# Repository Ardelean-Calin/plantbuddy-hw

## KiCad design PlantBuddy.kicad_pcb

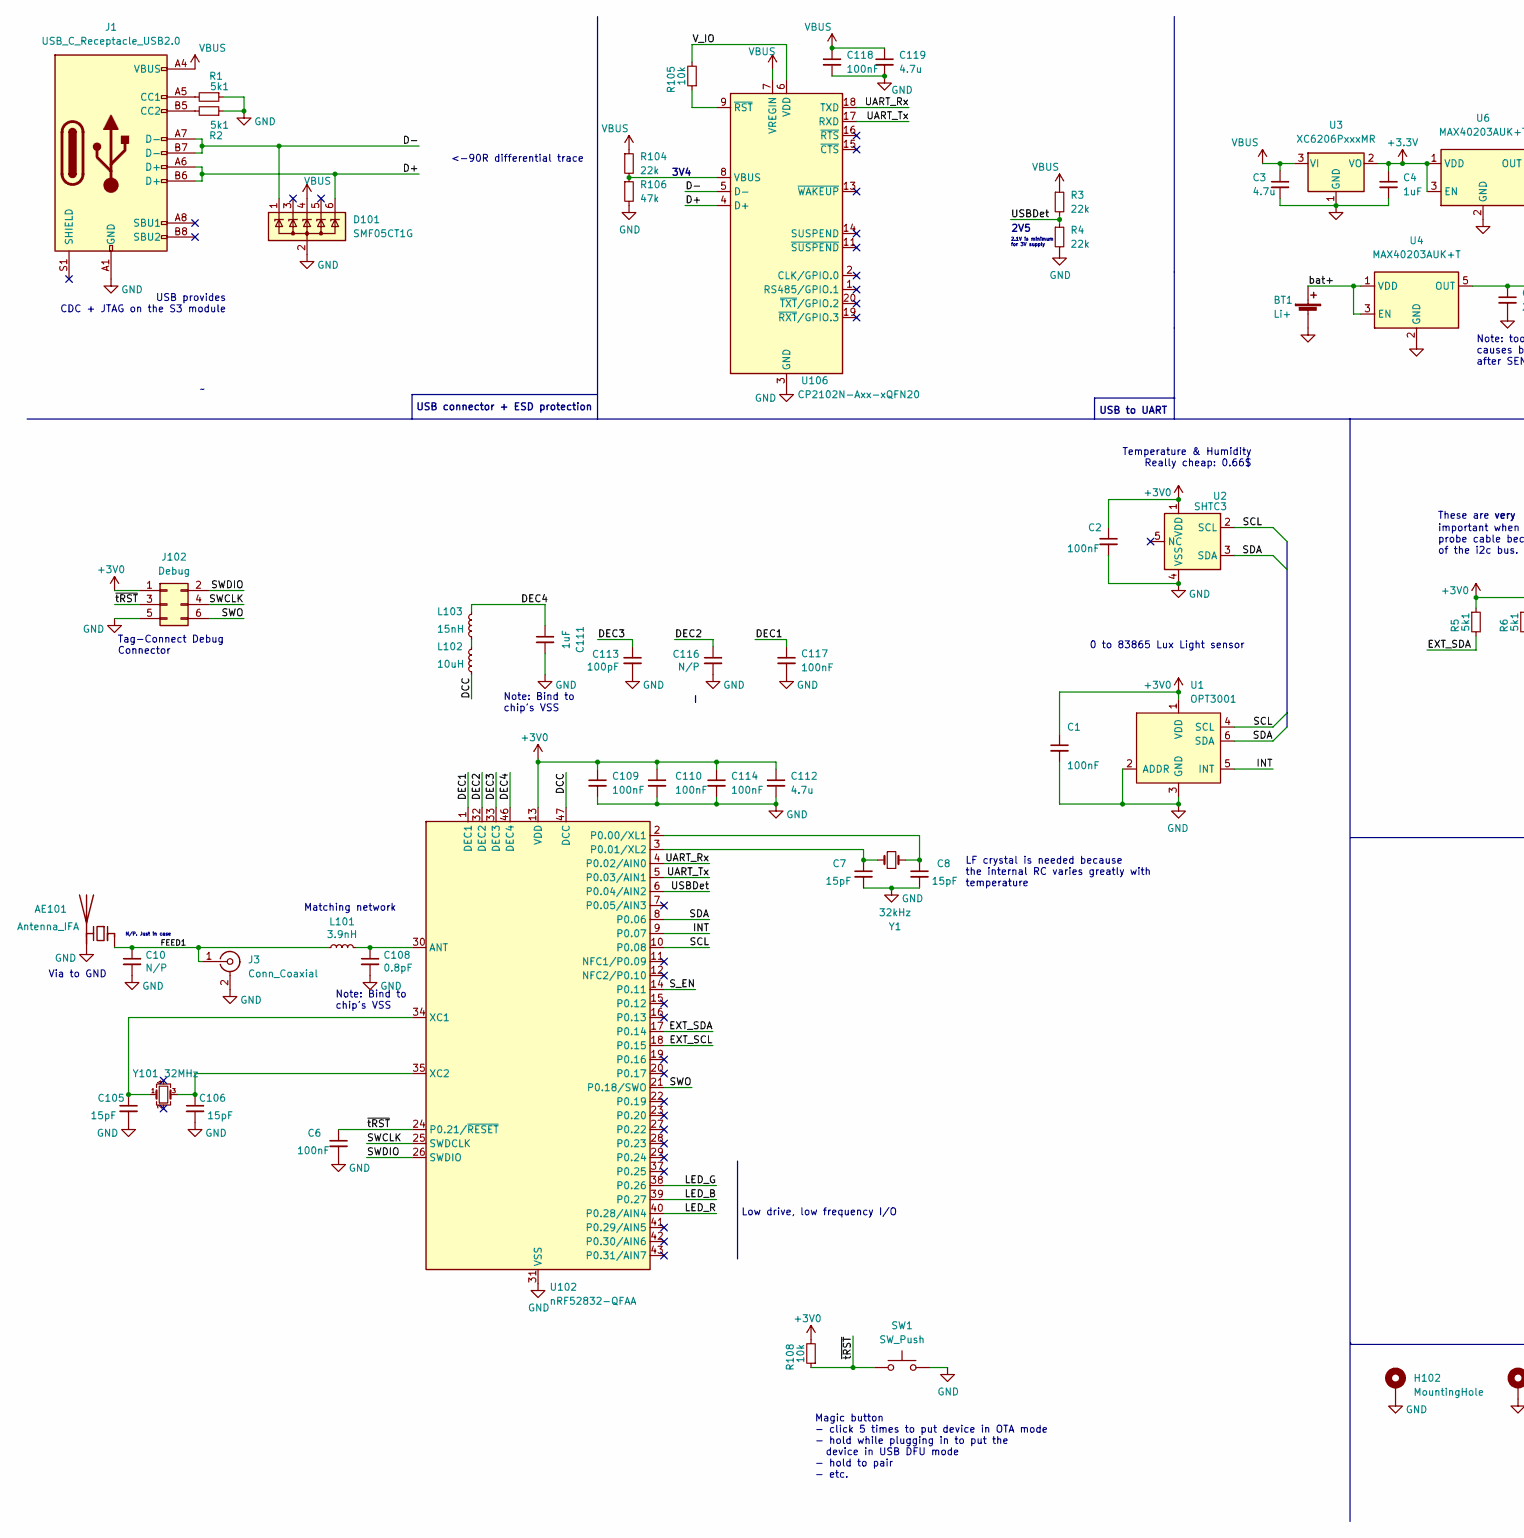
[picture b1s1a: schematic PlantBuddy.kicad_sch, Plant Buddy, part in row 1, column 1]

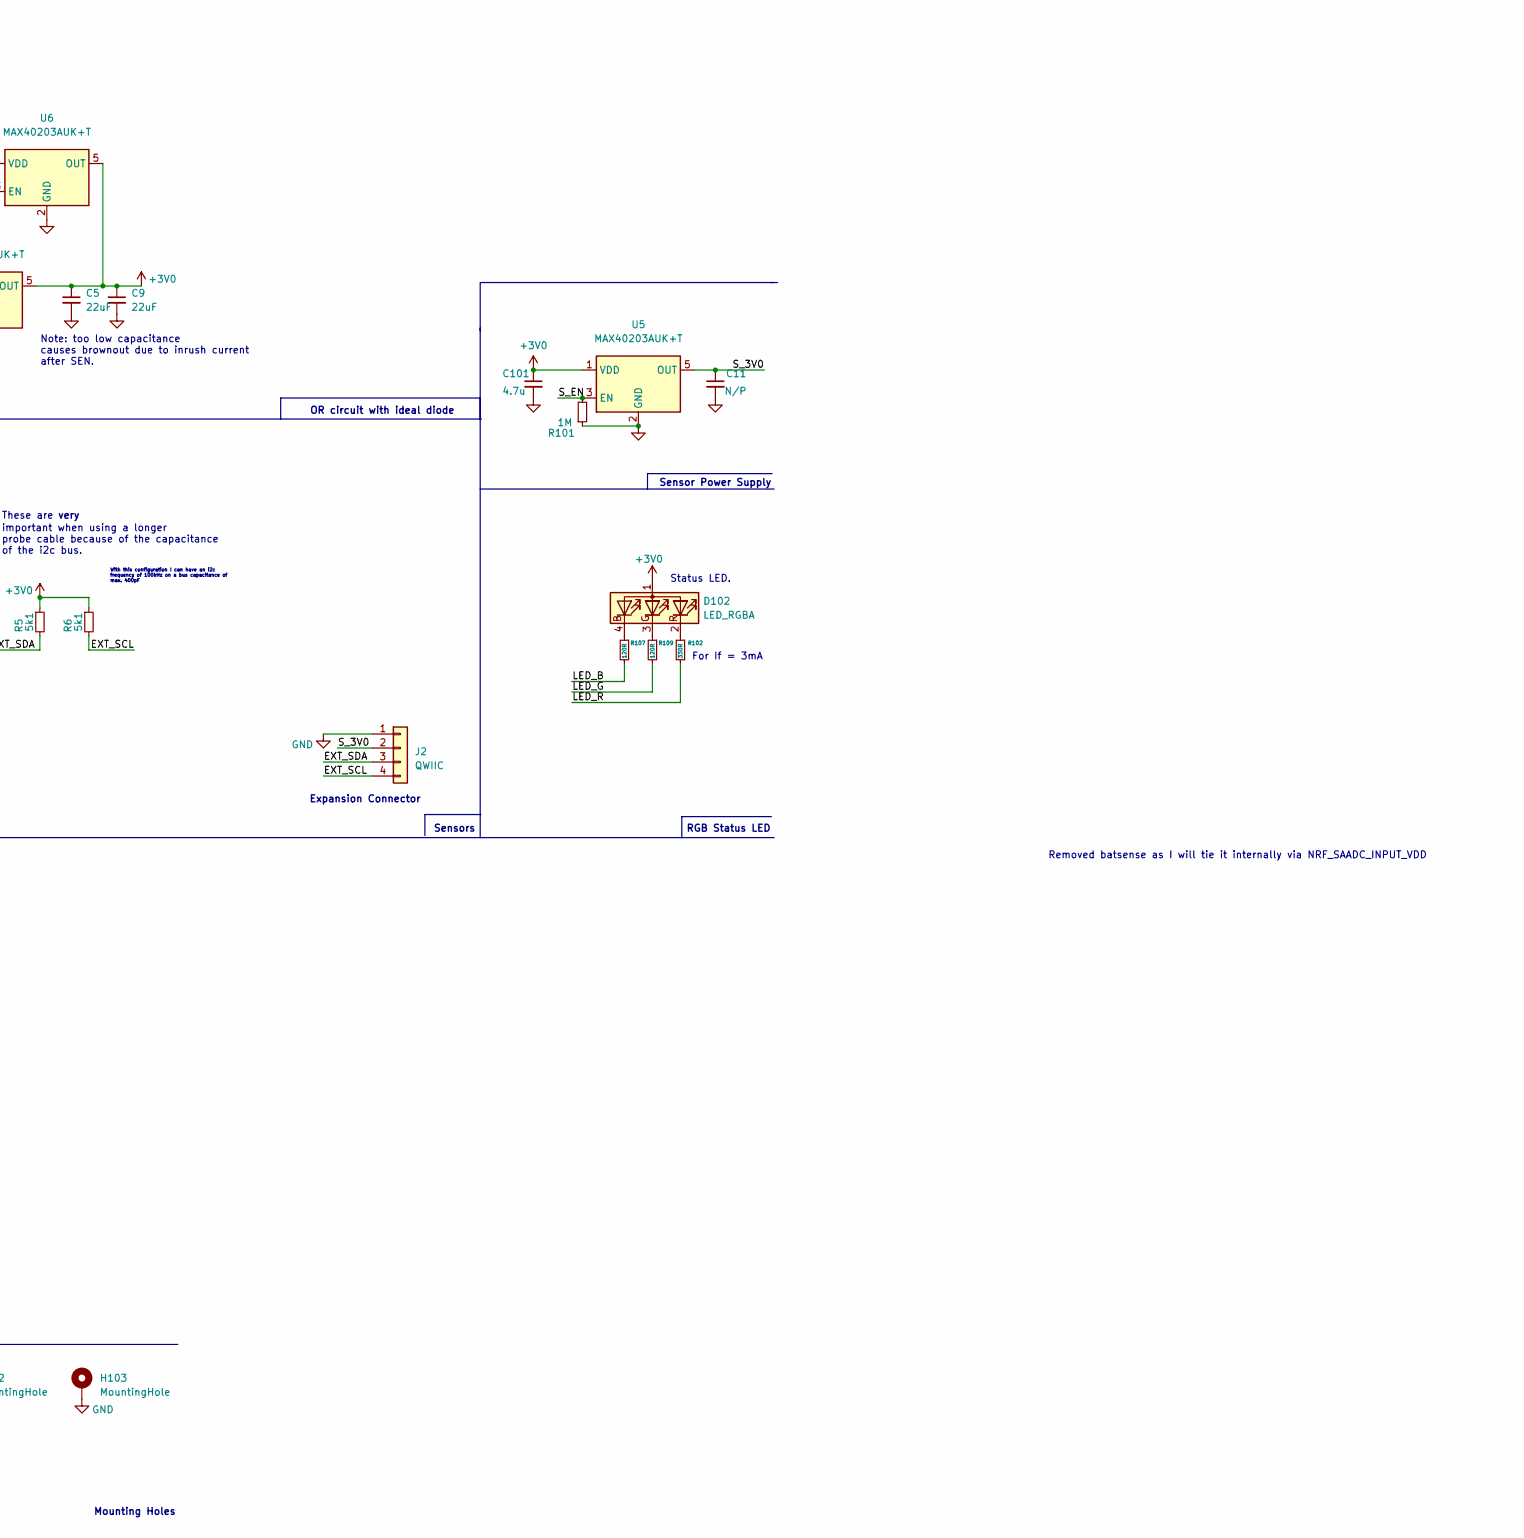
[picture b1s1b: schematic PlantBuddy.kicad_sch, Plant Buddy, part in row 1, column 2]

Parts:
AE101: Antenna_IFA; ANT-F-1-2.4G-1.6MM-FR4-WCH
BT1: Li+; BatteryHolder_LCSC_2032; LCSC C70377
C1, C2, C109, C110, C114, C117, C118: 100nF; C_0402_1005Metric; MPN CC0603KRX7R9BB104; LCSC C307331
C3, C101, C112, C119: 4.7u; C_0402_1005Metric; MPN CL10A475KO8NNNC; LCSC C23733
C4: 1uF; C_0402_1005Metric; MPN CL10A475KO8NNNC; LCSC C52923
C5, C9: 22uF; C_0603_1608Metric; MPN CL10A475KO8NNNC; LCSC C59461
C6: 100nF; C_0402_1005Metric; MPN CL10A475KO8NNNC; LCSC C307331
C7, C8, C105, C106: 15pF; C_0402_1005Metric; LCSC C1548
C10, C116: N/P; C_0402_1005Metric
C11: N/P; C_0402_1005Metric; MPN CL10A475KO8NNNC
C108: 0.8pF; C_0402_1005Metric; LCSC C172820
C111: 1uF; C_0402_1005Metric; MPN CC0603KRX7R9BB104; LCSC C52923
C113: 100pF; C_0402_1005Metric; LCSC C1546
D101: SMF05CT1G; SOT-363_SC-70-6; LCSC C15879
D102: LED_RGBA; LED_Lumex_SML-LX0404SIUPGUSB; LCSC C404280
H102, H103: MountingHole; MountingHole_3.2mm_M3_DIN965_Pad
J1: USB_C_Receptacle_USB2.0; USB_C_Receptacle_HRO_TYPE-C-31-M-12; MPN TYPE-C-31-M-12; LCSC C165948
J2: QWIIC; JST_SH_SM04B-SRSS-TB_1x04-1MP_P1.00mm_Horizontal; LCSC C160404
J3: Conn_Coaxial; U.FL_Hirose_U.FL-R-SMT-1_Vertical; LCSC C88374
J102: Debug; Tag-Connect_TC2030-IDC-NL_2x03_P1.27mm_Vertical
L101: 3.9nH; L_0402_1005Metric; LCSC C76775
L102: 10uH; L_0603_1608Metric; LCSC C223240
L103: 15nH; L_0402_1005Metric; LCSC C27143
R1, R2, R5, R6: 5k1; R_0402_1005Metric; MPN 0603WAF5101T5E; LCSC C25905
R3, R4, R104: 22k; R_0402_1005Metric; LCSC C25768
R101: 1M; R_0402_1005Metric; MPN 0603WAF2004T5E; LCSC C26083
R102: 330R; R_0402_1005Metric; LCSC C25104
R105, R108: 10k; R_0402_1005Metric; MPN 0603WAF5101T5E; LCSC C25744
R106: 47k; R_0402_1005Metric; LCSC C25792
R107, R109: 120R; R_0402_1005Metric; LCSC C25079
SW1: SW_Push; SW_Push_SPST_NO_Alps_SKRK; MPN SKRKAEE020; LCSC C115357
U1: OPT3001; SON65P200X200X65-7N; LCSC C90462
U2: SHTC3; SON100P200X200X80-5N; MPN SHTC3; LCSC C194656
U3: XC6206PxxxMR; SOT-23; LCSC C5446
U4, U5, U6: MAX40203AUK+T; SOT-23-5; LCSC C2653639
U102: nRF52832-QFAA; QFN-48-1EP_6x6mm_P0.4mm_EP4.6x4.6mm; LCSC C77540
U106: CP2102N-Axx-xQFN20; SiliconLabs_QFN-20-1EP_3x3mm_P0.5mm_EP1.8x1.8mm; LCSC C969913
Y1: 32kHz; Crystal_SMD_3215-2Pin_3.2x1.5mm; LCSC C32346
Y101: 32MHz; Crystal_SMD_3225-4Pin_3.2x2.5mm; LCSC C90934

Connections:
+3.3V: C4.1, U3.2 (VO), U6.1 (VDD), U6.3 (EN)
+3V0: C1.1, C2.1, C5.1, C9.1, C101.1, C109.1, C110.1, C112.1, C114.1, D102.1 (A), J102.1, R5.1, R6.1, R108.2, U1.1 (VDD), U2.1 (VDD), U4.5 (OUT), U5.1 (VDD), U6.5 (OUT), U102.13 (VDD), U102.36 (VDD), U102.48 (VDD)
/D+: D101.6 (K), J1.A6 (D+), J1.B6 (D+), U106.4 (D+)
/D-: D101.1 (K), J1.A7 (D-), J1.B7 (D-), U106.5 (D-)
/DCC: L102.2, U102.47 (DCC)
/DEC1: C117.1, U102.1 (DEC1)
/DEC2: C116.1, U102.32 (DEC2)
/DEC3: C113.1, U102.33 (DEC3)
/DEC4: C111.1, L103.1, U102.46 (DEC4)
/EXT_SCL: J2.4, R6.2, U102.18 (P0.15)
/EXT_SDA: J2.3, R5.2, U102.17 (P0.14)
/FEED1: AE101.1 (FEED), C10.1, J3.1 (In), L101.1
/INT: U1.5 (INT), U102.9 (P0.07)
/LED_B: R107.2, U102.39 (P0.27)
/LED_G: R109.2, U102.38 (P0.26)
/LED_R: R102.2, U102.40 (P0.28/AIN4)
/SCL: U1.4 (SCL), U2.2 (SCL), U102.10 (P0.08)
/SDA: U1.6 (SDA), U2.3 (SDA), U102.8 (P0.06)
/SWCLK: J102.4, U102.25 (SWDCLK)
/SWDIO: J102.2, U102.26 (SWDIO)
/SWO: J102.6, U102.21 (P0.18/SWO)
/S_3V0: C11.1, J2.2, U5.5 (OUT)
/S_EN: R101.2, U5.3 (EN), U102.14 (P0.11)
/UART_Rx: U102.4 (P0.02/AIN0), U106.18 (TXD)
/UART_Tx: U102.5 (P0.03/AIN1), U106.17 (RXD)
/USBDet: R3.2, R4.1, U102.6 (P0.04/AIN2)
/V_IO: R105.2, U106.6 (VDD)
/bat+: BT1.1 (+), U4.1 (VDD), U4.3 (EN)
/~tRST: C6.1, J102.3, R108.1, SW1.1, U102.24 (P0.21/~RESET)
GND: AE101.2 (PCB_Trace), BT1.2 (-), C1.2, C2.2, C3.2, C4.2, C5.2, C6.2, C7.2, C8.2, C9.2, C10.2, C11.2, C101.2, C105.2, C106.2, C108.2, C109.2, C110.2, C111.2, C112.2, C113.2, C114.2, C116.2, C117.2, C118.2, C119.2, D101.2 (A), H102.1, H103.1, J1.A1 (GND), J1.A12 (GND), J1.B1 (GND), J1.B12 (GND), J2.1, J3.2 (Ext), J102.5, R1.1, R2.1, R4.2, R101.1, R106.2, SW1.2, U1.2 (ADDR), U1.3 (GND), U1.7 (PAD), U2.4 (VSS), U3.1 (GND), U4.2 (GND), U5.2 (GND), U6.2 (GND), U102.31 (VSS), U102.45 (VSS), U102.49 (VSS), U106.3 (GND), U106.12 (GND), U106.21 (GND)
unnamed: D102.4 (BK), R107.1
unnamed: D102.3 (GK), R109.1
unnamed: D102.2 (RK), R102.1
unnamed: J1.A5 (CC1), R1.2
unnamed: J1.B5 (CC2), R2.2
unnamed: L102.1, L103.2
unnamed: C108.1, L101.2, U102.30 (ANT)
unnamed: C8.1, U102.2 (P0.00/XL1), Y1.2
unnamed: C7.1, U102.3 (P0.01/XL2), Y1.1
unnamed: C105.1, U102.34 (XC1), Y101.1
unnamed: C106.1, U102.35 (XC2), Y101.3
unnamed: R104.2, R106.1, U106.8 (VBUS)
unnamed: R105.1, U106.9 (~RST)
VBUS: C3.1, C118.1, C119.1, D101.4 (K), J1.A4 (VBUS), J1.A9 (VBUS), J1.B4 (VBUS), J1.B9 (VBUS), R3.1, R104.1, U3.3 (VI), U106.7 (VREGIN)

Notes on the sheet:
very
Sensors
Note: too low capacitance causes brownout due to inrush current after SEN.
These are
USB provides CDC + JTAG on the S3 module
Magic button - click 5 times to put device in OTA mode - hold while plugging in to put the device in USB DFU mode - hold to pair - etc.
Via to GND
RGB Status LED
Tag-Connect Debug Connector
Expansion Connector
Removed batsense as I will tie it internally via NRF_SAADC_INPUT_VDD
Sensor Power Supply
2.1V is minimum for 3V supply
important when using a longer probe cable because of the capacitance of the i2c bus.
Low drive, low frequency I/O
Note: Bind to chip's VSS
3V4
<-90R differential trace
0 to 83865 Lux Light sensor
Temperature & Humidity Really cheap: 0.66$
With this configuration I can have an i2c frequency of 100kHz on a bus capacitance of max. 400pF
Matching network
Mounting Holes
For If = 3mA
LF crystal is needed because the internal RC varies greatly with temperature
2V5
OR circuit with ideal diode
Status LED.
N/P. Just in case
USB connector + ESD protection
USB to UART

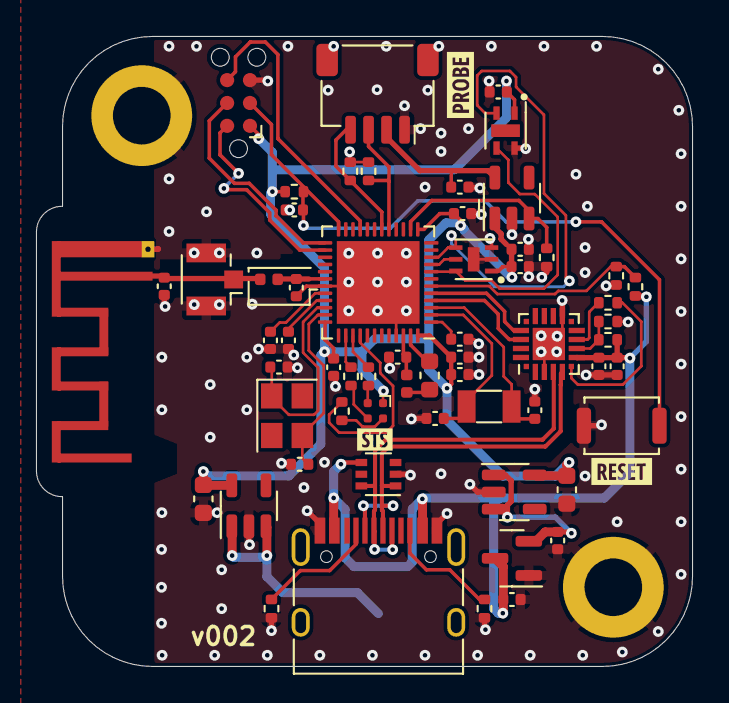
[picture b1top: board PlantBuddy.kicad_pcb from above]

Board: 4 copper layers, 36.4 x 35.0 mm, 63 parts (1 on the bottom side), 44 nets.

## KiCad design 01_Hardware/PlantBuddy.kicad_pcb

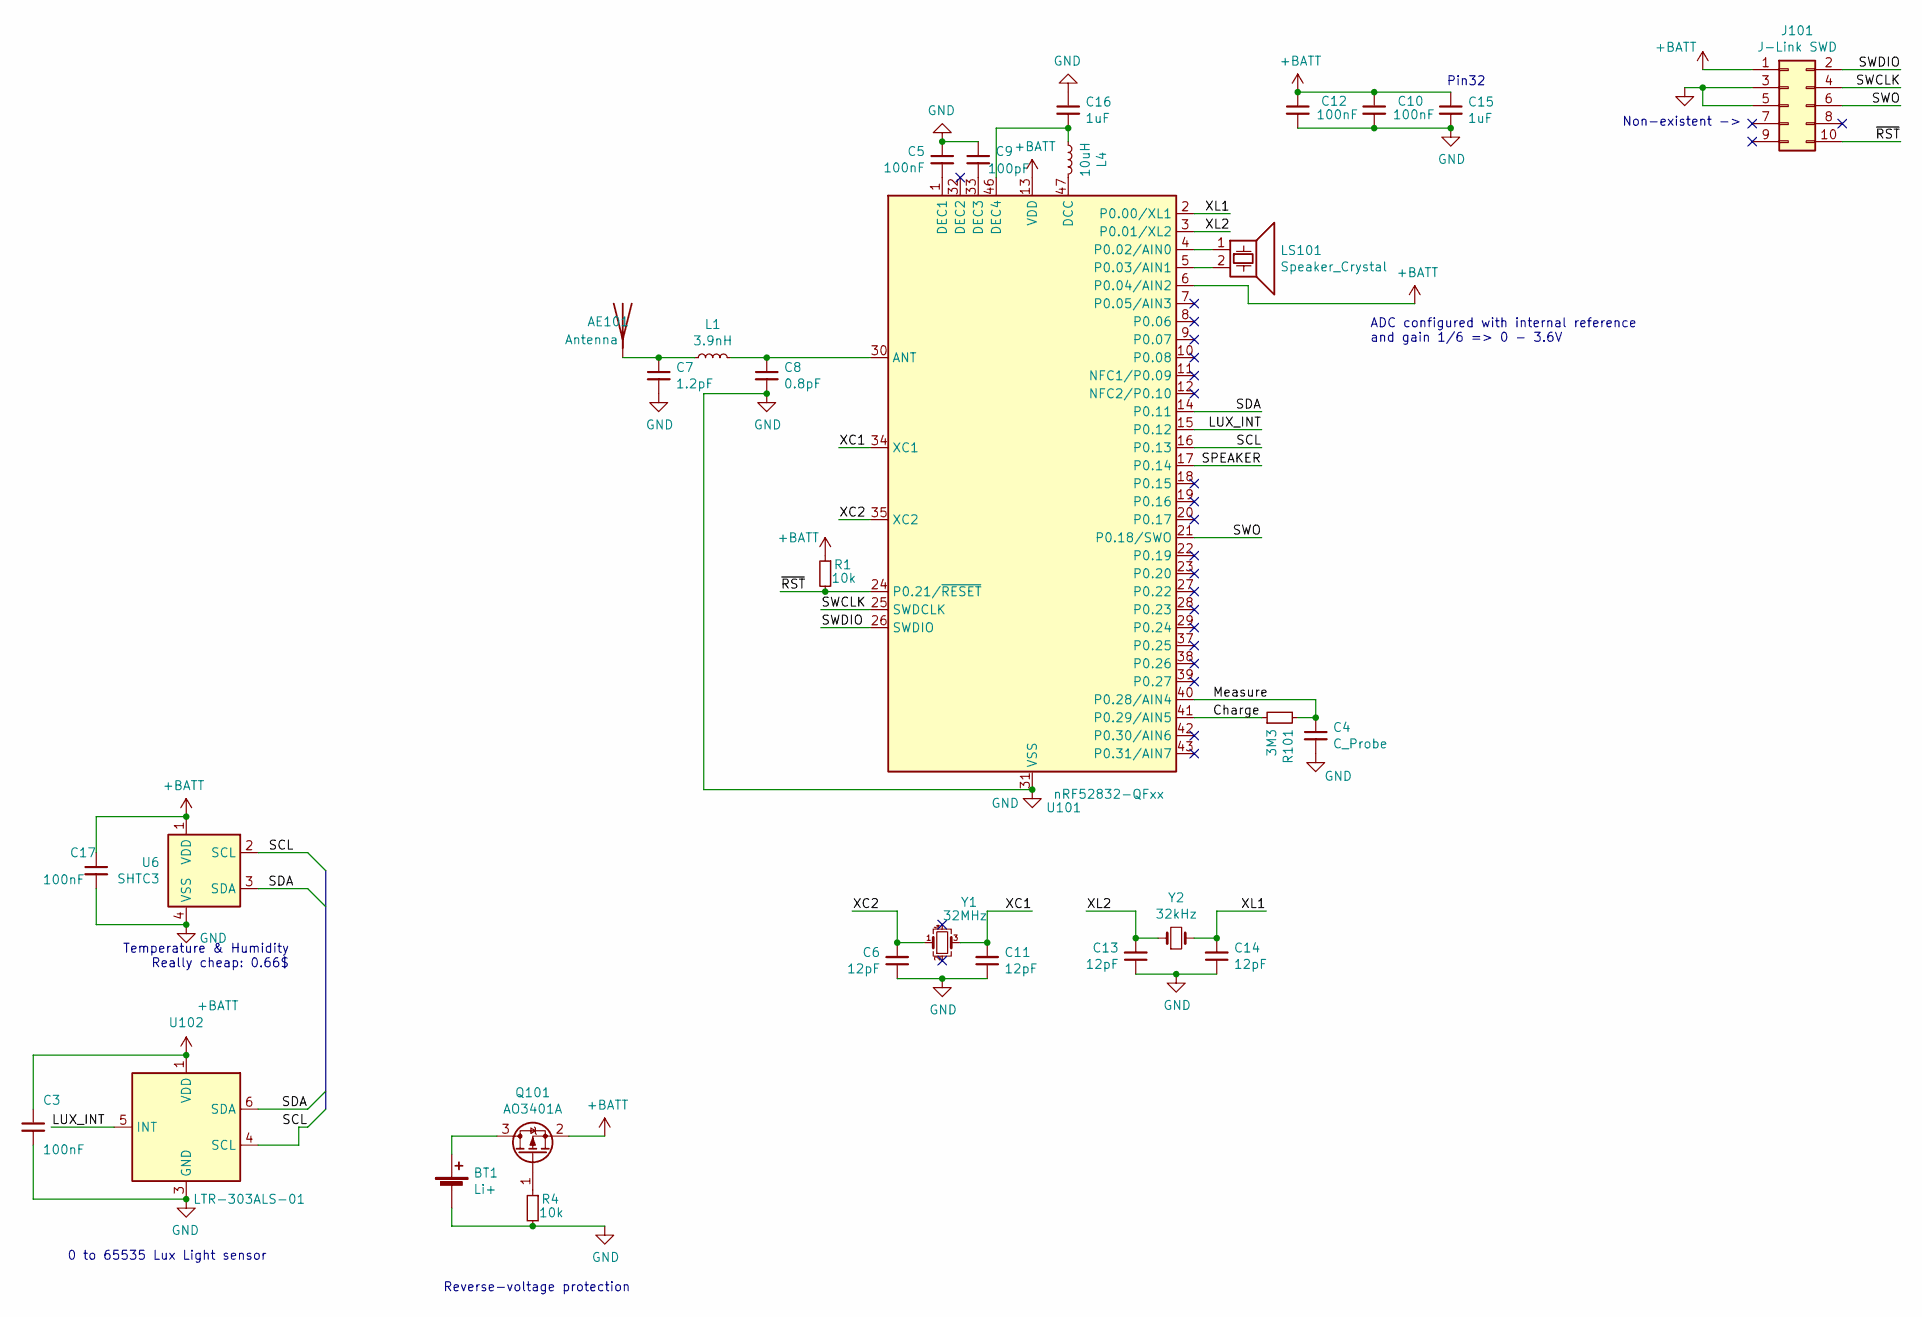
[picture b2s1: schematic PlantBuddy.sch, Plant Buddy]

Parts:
AE101: Antenna; monopole
BT1: Li+; BAT-HLD-001
C3, C5, C10, C12, C17: 100nF; C_0603_1608Metric; LCSC C1525
C4: C_Probe; SoilProbe
C6, C11, C13, C14: 12pF; C_0603_1608Metric; LCSC C1547
C7: 1.2pF; C_0402_1005Metric; LCSC C159809
C8: 0.8pF; C_0402_1005Metric; LCSC C285068
C9: 100pF; C_0402_1005Metric; LCSC C1546
C15, C16: 1uF; C_0603_1608Metric; LCSC C52923
J101: J-Link SWD; PinHeader_2x05_P1.27mm_Vertical_SMD
L1: 3.9nH; L_0402_1005Metric; LCSC C14033
L4: 10uH; L_0805_2012Metric; LCSC C95978
LS101: Speaker_Crystal; PinHeader_1x02_P2.54mm_Vertical
Q101: AO3401A; SOT-23
R1, R4: 10k; R_0603_1608Metric; LCSC C25744
R101: 3M3; R_0603_1608Metric; LCSC C25741
U6: SHTC3; Sensirion_DFN-4-1EP_2x2mm_P1mm_EP0.7x1.6mm; LCSC C194656
U101: nRF52832-QFxx; QFN-48-1EP_6x6mm_P0.4mm_EP4.6x4.6mm_ThermalVias
U102: LTR-303ALS-01; Lite-On_LTR-303ALS-01
Y1: 32MHz; Crystal_SMD_3225-4Pin_3.2x2.5mm; LCSC C90934
Y2: 32kHz; Crystal_SMD_3215-2Pin_3.2x1.5mm; LCSC C32346

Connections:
+BATT: C3.1, C10.1, C12.1, C15.1, C17.1, J101.1, Q101.2 (S), R1.1, U6.1 (VDD), U101.6 (P0.04/AIN2), U101.13 (VDD), U101.36 (VDD), U101.48 (VDD), U102.1 (VDD)
/Charge: R101.1, U101.41 (P0.29/AIN5)
/LUX_INT: U101.15 (P0.12), U102.5 (INT)
/Measure: C4.1, R101.2, U101.40 (P0.28/AIN4)
/SCL: U6.2 (SCL), U101.16 (P0.13), U102.4 (SCL)
/SDA: U6.3 (SDA), U101.14 (P0.11), U102.6 (SDA)
/SPEAKER: U101.17 (P0.14)
/SWCLK: J101.4, U101.25 (SWDCLK)
/SWDIO: J101.2, U101.26 (SWDIO)
/SWO: J101.6, U101.21 (P0.18/SWO)
/XC1: C11.2, U101.34 (XC1), Y1.3
/XC2: C6.2, U101.35 (XC2), Y1.1
/XL1: C14.2, U101.2 (P0.00/XL1), Y2.2
/XL2: C13.2, U101.3 (P0.01/XL2), Y2.1
/~RST: J101.10, R1.2, U101.24 (P0.21/~RESET)
GND: BT1.2 (-), C3.2, C4.2, C5.1, C6.1, C7.2, C8.2, C9.1, C10.2, C11.1, C12.2, C13.1, C14.1, C15.2, C16.1, C17.2, J101.3, J101.5, R4.2, U6.4 (VSS), U101.31 (VSS), U101.45 (VSS), U101.49 (VSS), U102.3 (GND)
unnamed: AE101.1, C7.1, L1.1
unnamed: BT1.1 (+), Q101.3 (D)
unnamed: C5.2, U101.1 (DEC1)
unnamed: C8.1, L1.2, U101.30 (ANT)
unnamed: C9.2, U101.33 (DEC3)
unnamed: C16.2, L4.1, U101.46 (DEC4)
unnamed: L4.2, U101.47 (DCC)
unnamed: LS101.1, U101.4 (P0.02/AIN0)
unnamed: LS101.2, U101.5 (P0.03/AIN1)
unnamed: Q101.1 (G), R4.1

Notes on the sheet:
Temperature & Humidity Really cheap: 0.66$
Reverse-voltage protection
0 to 65535 Lux Light sensor
ADC configured with internal reference and gain 1/6 => 0 - 3.6V
Pin32
Non-existent ->

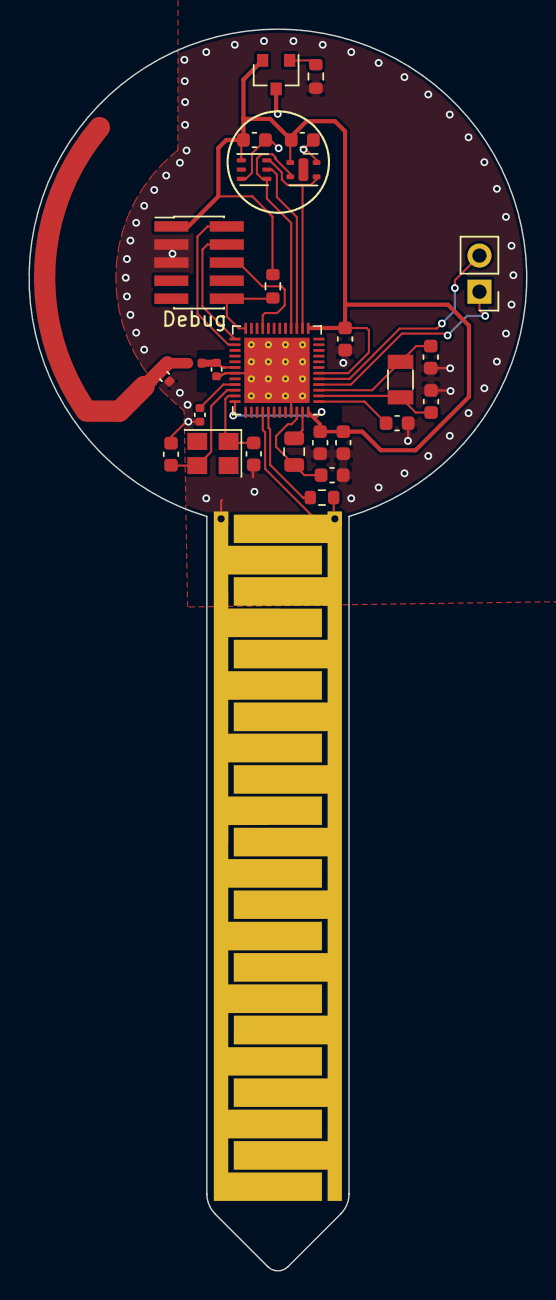
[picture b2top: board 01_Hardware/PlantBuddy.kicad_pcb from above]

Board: 2 copper layers, 35.0 x 87.3 mm, 30 parts (1 on the bottom side), 25 nets.

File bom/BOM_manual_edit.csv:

Comment,Designator,Footprint,LCSC Part Number
1.2pF,C7,0402,C159809
0.8pF,C8,0402,C285068
100pF,C9,0603,C14858
100nF,"C3,C5,C10,C12,C17",0603,C14663
12pF,"C6,C11,C13,C14",0603,C38523
1uF,"C15,C16",0603,C15849
SWD Debug port,J101,HDR-SMD,C150517
3.9nH,L1,0402,C14033
10uH,L4,0805,C1046
P-Channel Mosfet,Q101,SOT-23-3L,C15127
10k,"R1,R4",0603,C25804
0 Ohm,R101,0603,C21189
10 Ohm,R102,0603,C22859
Temperature & humidity,U6,DFN-4,C194656
"Nordig nRF52 SoC I2C, SPI, UART 4dBm 1.7V ~ 3.6V TxRx + MCU 2.4GHz QFN-48_6x6x04P RF Transceiver ICs ROHS",U101,QFN-48_EP_6.0x6.0x0.4P,C77540
SMD Ambient Light Sensors ROHS,U102,6-pin chipled package,C364577
±10ppm 12pF -20℃~70℃ 贴片无源晶振 60Ω 32000000Hz SMD3225-4P Crystals ROHS,Y1,SMD-3225_4P,C90934
-40℃~85℃ 32768Hz 12.5pF 贴片无源晶振 ±20ppm 70kΩ SMD3215-2P Crystals ROHS,Y2,SMD-3215_2P,C32346

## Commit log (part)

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2020-10-13 Backup. Schematic done, I think
2020-10-13 PCB almost done
2020-10-14 Initial Layout done
2020-10-15 Ordered PCB
2020-11-05 Added FreeRTOS
2020-11-05 Removed .bin file
2020-11-05 Added useful docs
2020-11-05 Cleanup
2020-11-05 Changed LED frequenct
2020-11-05 Refactored openocd config
2020-11-05 Added support for better debug handling
2020-11-08 Added SHT21 datasheet
2020-11-10 Removed STM32CubeMx file
2020-11-10 SHT2X initial code
2020-11-11 Basic SHT2X temperature logging
2020-11-12 Air Temperature and Humidity now working! 🌡🌧
2020-11-17 Configured timer for soil humidity measurement.
2020-11-17 Migrated settings to workspace.
2020-11-18 Added portmacro to includes.
2020-11-19 Separated functionality into modules.
2020-11-19 Soil humidity measurement working!
2020-11-23 Slight refactoring of SHT2X module. Still can't go low-power
2020-11-23 Reduced tick frequency in preparation for low-power
2020-11-23 Lengthened soilhumidity task duration
2020-11-23 Added BLE stack and LP stack
2020-11-26 Added low-power configuration for SHT2X
2020-11-26 Made the soil humidity frequency variable global
2020-11-26 Started schematic revision
2020-11-28 Revised schematic
2020-11-28 Revised PCB
2020-11-28 Ordered PCB version 2
2020-12-05 Added a delay to the BLE task
2020-12-05 Changed tick frequency to 100Hz
2020-12-14 Received PlantBuddy v2. Fixed some stuff
2020-12-14 Corrected BLE module
2020-12-24 Now reading RH and T with new sensor
2020-12-31 Refactored i2c module & SHT2C driver
2021-01-01 Started communicating with lux sensor
2021-01-03 Slight adaptation to Bluetooth config file
2021-01-03 Added OTA document
2021-01-03 Removed unused function
2021-01-06 Switched to CMAKE
2021-01-07 Separated firmware into app and bootloader
2021-01-08 Updated memory layout to reseerve first 192B of RAM for vector table.
2021-01-08 Updated to latest bootloader
2021-01-15 Moved to Linux
2021-01-15 Linux compatibility adaptations.
2021-01-29 Switched to nRF52810.
2021-02-05 Switched to nRF52810
2021-02-06 Created simple blink example.
2021-02-06 Added debug possibility & modules
2021-02-09 Preliminary routing of GPIO to Counter using PPI.
2021-02-09 Sorted files.
2021-02-09 Preliminary version of soil humidity
2021-02-09 Removed empty line.
2021-02-11 Refactored soil humidity measurement.
2021-02-11 Formatted sdk_config with clang-format.
2021-02-11 Reset Makefile and disabled logging => lots of space!
2021-02-15 Added more VSCode tasks.
2021-02-15 Removed cortex-debug state info
2021-02-15 Soil humidity now working!
2021-02-15 Added BLE App header!
2021-02-15 Removed unnecessary defines & enabled TWI transaction manager.
2021-02-15 SHTC3 temperature and humidity now working!
2021-02-15 Added define for us delay.
2021-02-15 Added documentation to SHTC3 driver.
2021-02-16 OPT3001 driver done.
2021-02-16 Fixed Lux reading.
2021-02-16 Added battery sensor module.
2021-02-17 Added basic BLE functionality.
2021-02-17 Added secure bootloader workflow. For now just builds.
2021-02-17 Bootloader now working!
2021-02-17 Added app flashing task
2021-02-18 Updated DFU name.
2021-02-18 Slight improvements.
2021-02-18 Added micro-ecc
2021-02-18 Added Dependency
2021-02-18 Added buttonless DFU functionality!
2021-02-18 Added debug flag
2021-02-18 Changed frequency of status LED blinking
2021-02-19 Added util folder with UUID script
2021-02-19 Set BLE appearance.
2021-02-19 Incipient work on custom service.
2021-02-23 Small clean-up.
2021-02-23 Restructured application project.
2021-02-25 Removed modules no longer in use.
2021-02-25 Added micro-ecc module properly!
2021-02-25 Backup.
2021-02-25 Slight adaptation after porting to THE BEAST.
2021-02-25 Added different debug name.
2021-02-25 Added soil humidity characteristic.
2021-02-25 Slight hardware changes.
2021-02-25 Added air temperature and humidity characteristics
2021-02-25 Removed some lines.
2021-02-26 Fixed incorrect lux value.
2021-02-27 Simplified BLE characteristics!
2021-03-05 Revised 3d models a bit
2021-03-09 Slight PCB modifications
2021-03-10 Changed to two-layer PCB
2021-03-10 Slight modifications to two-layer version
2021-03-11 Added passthrough link to Readme
2021-03-11 Ordered 2-layer PCB from PCBway
2021-03-11 Moved mobile app
2021-03-11 Renamed mobile app.
2021-03-13 Improved CPU performance by ~20%
2021-03-22 Lowered sensor data aquisition time to reduce power.
2021-03-22 Removed private key from gitignore.
2021-03-22 Updated KVM config.
2021-03-22 Updated 3D model
2021-04-01 Added windows config.
2021-04-07 Now advertising correct service.
2021-04-13 Enabled PIN-based pairing.
2021-04-19 Added better logging capability.
2021-04-19 Fixed some include errors.
2021-04-26 Fixed BLE UUIDs
2021-04-26 Added timestamp to BLE characteristic. Switched to human-readable representation of humidity and temperature in data packet. Added jupyter notebook that extracts all sensor data.
2021-04-27 Renamed characteristic.
2021-04-27 Code cleanup & refactoring.
2021-04-27 Added battery voltage to sensor package (temporary)
2021-04-28 Removed static PIN and made slight adaptations to RELEASE
2021-04-28 Switched to pipenv for python code.
2021-04-29 Added jupyter to pipfile.
2021-04-29 Moved headers near the source.
2021-04-29 Moved unix time to self contained module.
2021-06-11 Slight makefile update.
2021-08-01 Restarted app development using PWA.
2021-08-02 Backup before migration to GitLAB
2021-08-04 Basic reading of characteristics working in web-ui.
2021-08-06 Just some small UPPER-CASE correction
2021-08-06 Changed to the recommended version of GCC - always use this!
2021-08-06 Added logging via UART.
2021-08-06 Added serial-port debug.
2021-08-06 Created better task scheduling.
2021-08-06 Improvements to task scheduler.
2021-08-06 Still task scheduler improvements.
2021-08-10 Started developing downloader... might delete later.
2021-08-11 Added devcontainer using docker! 🎉🐋
2021-08-11 Added some info regarding groups.
2021-08-11 Re-added phone app now with docker! 🐋
2021-08-11 Added emulator to path.
2021-08-14 Slight container changes.
2021-08-14 PlantBuddy Revision 3. Switched to nRF52832
2021-08-16 HW: Rev 4.1 => Changed ALS from OPT3001 to LTR-303
2021-08-16 Initial template for plant presentation page.
2021-08-18 Further UI changes.
2021-08-20 PhoneApp: Implemented safezone indicator.
2021-08-20 PhoneApp: Added really nice plot.
2021-09-04 Started PCB improvements & added SVGs and interactive BOM.
2021-09-05 Embedded: Added preliminary JLink support.
2021-09-05 Embedded: Preliminary support of nRF52832.
2021-09-06 Embedded: Simplified launch.json.
2021-09-06 Embedded: Removed soilhum code references in preparation for new implementation.
2021-09-06 PCB: Changed name of net.
2021-09-06 Embedded: Code cleanup.
2021-09-07 Removed openjdk requirement.
2021-09-07 Added X11 forwarding.
2021-09-09 Added Ozone debugger support!
2021-09-09 Corrected device identifier.
2021-09-09 Added better debug flags.
2021-09-10 Embedded: found culprit for crash: SAADC can't work together with CSENSE
2021-09-10 Changed antenna design to monopole
2021-09-10 Switched to 0603 and re-did layout.
2021-09-10 Slight adjustments to Antenna ground plane & length.
2021-09-10 Slight changes to RF trace width.
2021-09-14 Added plugnplay xserver support via configuration.
2021-09-28 Updated interactive BOM
2021-09-28 Adapted firmware to run on latest development board from AISLER.
2021-09-28 Incipient LTR303 driver.
2021-09-29 LTR-303 now works.
2021-09-29 Refactoring.
2021-10-01 All sensors now working!
2021-10-01 Added smarter NRF_LOG toggle.
2021-10-18 Updated gitmodules path
2021-10-18 Slight changes to dockerfile
2021-10-19 Switched to podman.
2021-10-20 Removed Phone app from main repo
2021-10-20 Modified gitmodule path
2021-10-20 Removed firmware
2021-10-20 Re-added firmware as submodule
2021-10-20 Updated firmware
2021-11-09 Added current sense resistor & COMP resistor.
2021-11-10 Corrected PCB BOM.
2022-04-21 Switched to ESP32
2022-04-29 Had to change the way we do capacitive soil humidity.
2022-05-05 Added tooling holes.
2022-05-06 Added reverse voltage protection; status LED; changed resistance of green LED; changed piezo footprint
2022-05-27 Simplified capacitance measurement
2022-06-15 Temperature calibrated capacitive sensing & ordered from JLCPCB
2022-06-19 Removed previous CPL file
2022-06-27 New board based on ESP32-S3 mostly done. Waiting for part availability...
2022-06-28 Silkscreen & testpoints
2022-06-28 Changed pin layout to have more EXT pins
2022-06-30 Added different mezzannine connector
2022-07-02 Added 3D models for everything
2022-07-03 Created a 2-layer board variant.
2022-07-03 Small cleanup & impedance matching
2022-07-03 Rounded slot of sensor area
2022-07-03 Removed gerbers from source control
2022-07-03 Created better .step file
2022-07-04 Separated temperature sensor ground plane
2022-07-19 Fixed 3D model of USB-C connector
2022-07-22 Converted to proper 4-layer and ordered PCB
2022-07-22 Removed ground plane under antenna
2022-07-26 Fixed board after first batch arrived. Changed connector to FFC.
2022-07-26 Fixed hole sizes
2022-07-28 Made copper fill under temperature sensor bigger.
2022-07-30 Moved temp mid to ADC1_CH8 & batsense to ADC1_CH7. To note: only ADC1 can be used if WiFi is enabled!
2022-08-14 Changed 100nF capacitors to 0402
2022-08-14 Removed current shunt & generated build files.
2022-08-18 Switched to ESP32-S3-Mini and changed PCB shape
2022-08-20 Multitude of changes. Hopefully design freeze.
    - Switched JST connector to a bigger 2mm pitch one.
    - Added battery protection circuit for coin cell.
    - Created cutout in PCB for battery cable.
    - Added heatsink for SHTC3.
    - Added plated mounting holes for looks and power dissipation.
    - Changed pin layout to facilitate wake-up via USB-C plug-in detection.
2022-08-22 Added Voltage Supervisor circuit.
    LMS33460 is used as a voltage supervisor circuit meant to protect the
    ESP32, as well as the battery, if a low-voltage condition is detected.
2022-08-22 Generated latest STL model.
2022-08-22 Changed CR2450 holder to cheaper, non-plated one.
2022-08-31 Fixes & ordered.
2022-08-31 Slight BOM consolidation.
    - Changed 9.1k resistor to a 10k one.
    - Changed 470k resistor to a 1Meg one.
2022-09-04 Major PCB changes.
    - Added inductor for nRF52 DCDC converter.
    - Moved USB-C connector to bottom left.
    - Moved USB charger and battery protection IC.
    - Moved USB-to-serial converter.
    - Changed pinout to simplify routing.
2022-09-21 Added proper MPN for Nordic chip
2022-09-22 Moved antenna
2022-09-23 Last order before main order. NO MORE ORDERS ALLOWED
2022-09-25 Added voltage monitoring IC. Shuts everything down if Vbat < 3V
2022-09-26 Exchanged debug connector for Tag-Connect TC2030-CTX-NL
2022-09-26 Added JLCPCB tooling holes & moved mounting holes.
2022-09-29 Switched LDO to a better, brand-name one.
    - Also am now powering the i2c sensors directly from the LDO because I
    noticed current spikes in the previous EN -> measure -> DIS
    implementation.
2022-10-07 Changed antenna configuration back.
    After testing I found out that this antenna configuration works
    better.
2022-11-03 Changed to IFA antenna
2022-11-08 Changed antenna to 1.6mm-compatible one
2022-11-21 Added probe as submodule
2022-11-29 Added probe present detection via EXT8.
2022-12-08 Connected button to reset pin
2022-12-20 Created and ordered a non-rechargeable version.
2023-01-04 Enhanced silkscreen layer.
2023-01-07 Fixed probe not working due to brownout
2023-01-08 PCB changes after testing.
    - separated i2c buses
    - changed layer stackup to sig-gnd-gnd-sig
    - added top & bottom ground layers
    - routed power on bottom layer
    - added LF crystal
2023-01-08 Tuned USB differential pair
2023-01-09 Added solder-mask over antenna.
2023-01-09 Switched ALS to OPT3001
2023-01-09 Added N/P capacitor at the output of SEN.
2023-01-11 Made the first production order. 30pcs
2023-02-16 Moved USB-C connector outwards.
2023-03-10 Switched to nRF52840.
2023-05-04 Switched to QWIIC/STEMMA-QT
2023-05-10 Started Sensus v2 with ESP32-C3
2023-05-15 Ordered boards
2023-05-15 Generated gerbers & updated probe commit
2023-06-27 Changed connector to QWIIC & moved USB-C lower
2023-06-27 Added U.FL connector and moved antenna.
